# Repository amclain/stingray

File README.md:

# Stingray

Build farm automation and remote management.

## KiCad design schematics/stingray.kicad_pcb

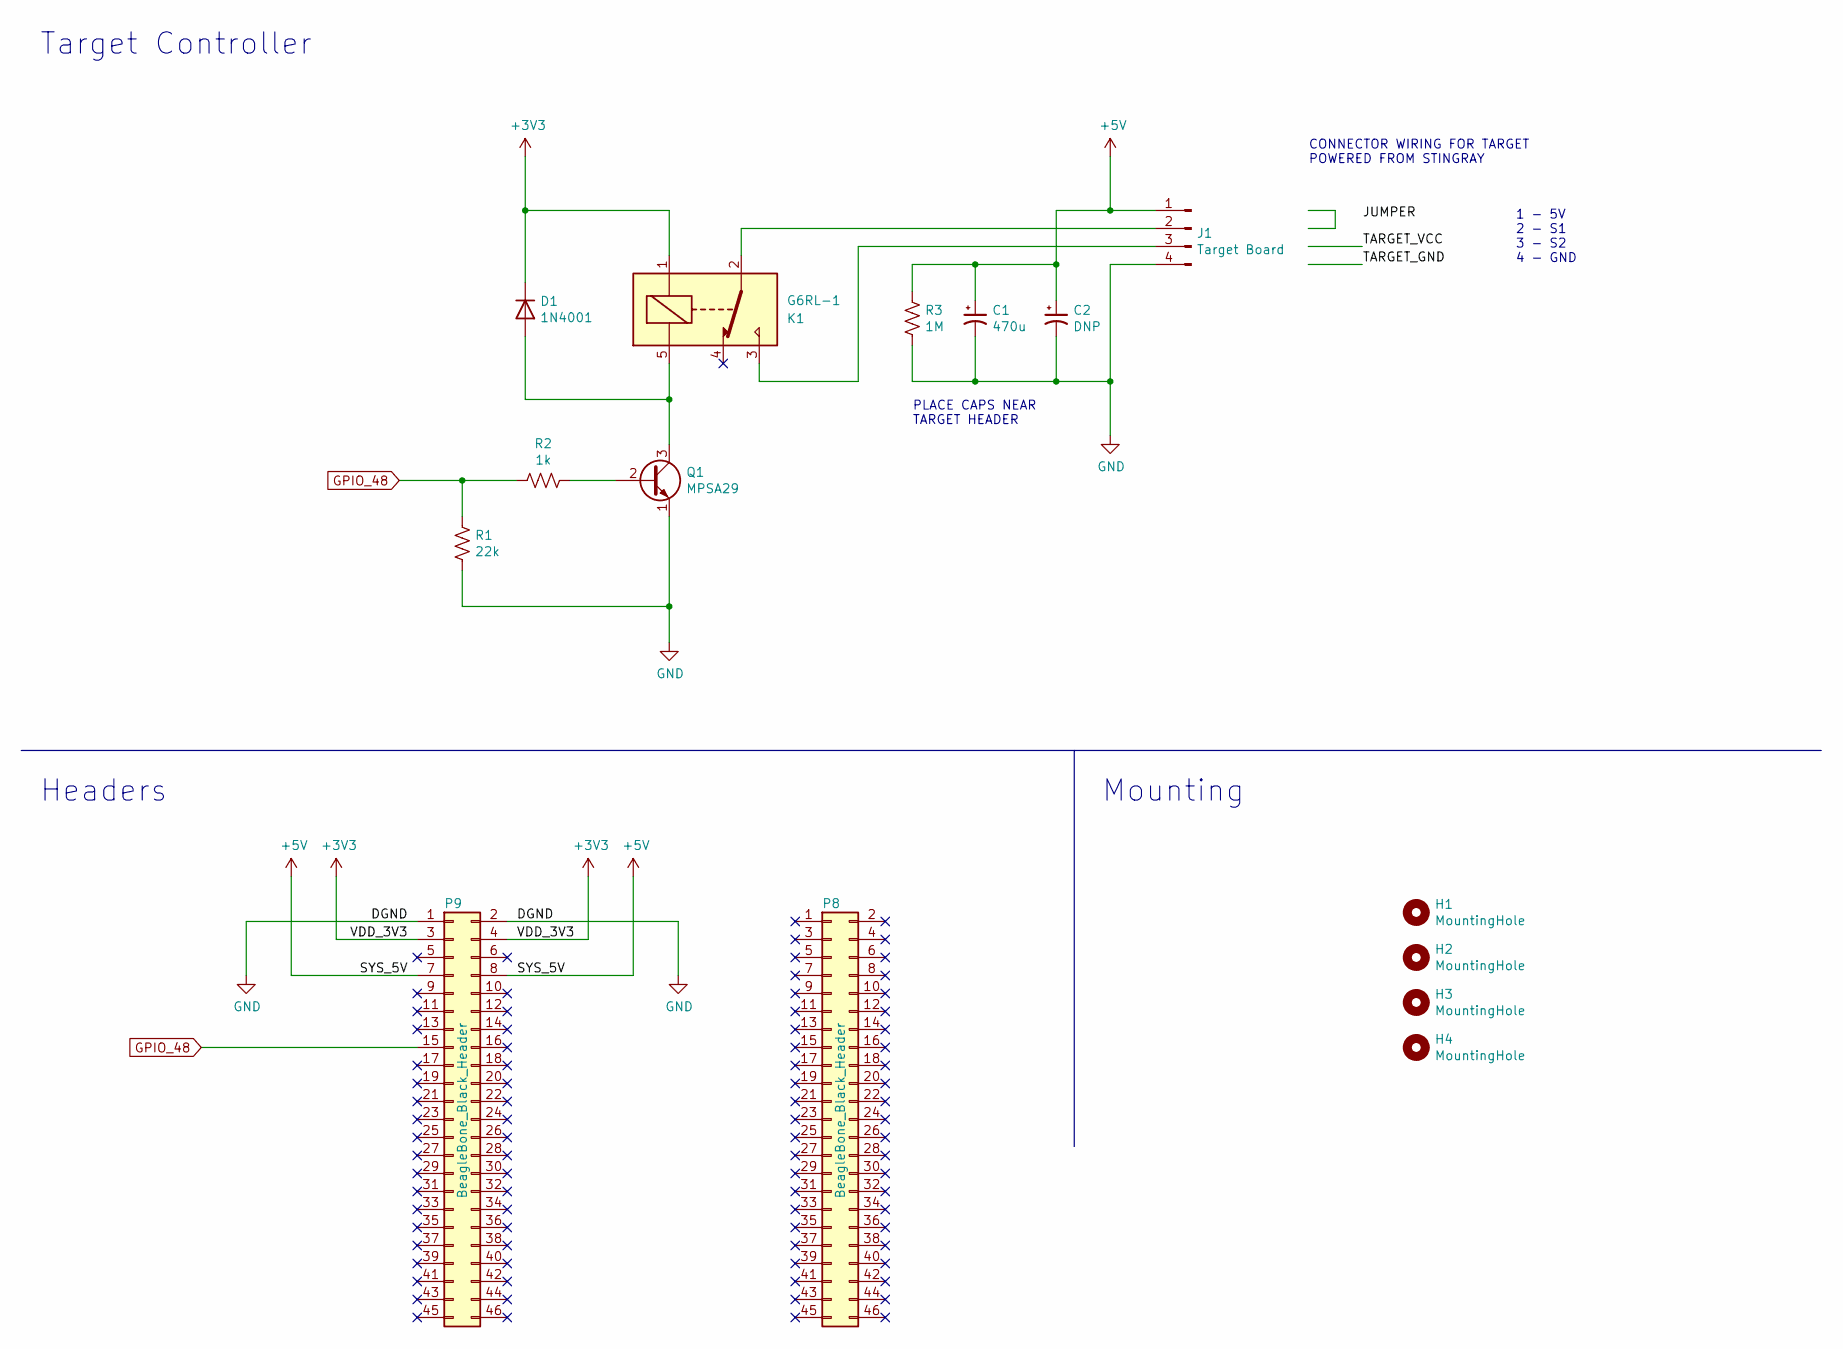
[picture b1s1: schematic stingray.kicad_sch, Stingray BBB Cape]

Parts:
C1: 470u; CP_Radial_D8.0mm_P5.00mm
C2: DNP; CP_Radial_D8.0mm_P5.00mm
D1: 1N4001; D_DO-41_SOD81_P10.16mm_Horizontal
H1, H2, H3, H4: MountingHole; MountingHole_3.2mm_M3
J1: Target Board; PhoenixContact_MC_1,5_4-G-3.81_1x04_P3.81mm_Horizontal
K1: G6RL-1; Relay_SPDT_Omron_G6RL-1
P8, P9: BeagleBone_Black_Header; Socket_BeagleBone_Black
Q1: MPSA29; TO-92_Inline
R1: 22k; R_Axial_DIN0207_L6.3mm_D2.5mm_P10.16mm_Horizontal
R2: 1k; R_Axial_DIN0207_L6.3mm_D2.5mm_P10.16mm_Horizontal
R3: 1M; R_Axial_DIN0207_L6.3mm_D2.5mm_P10.16mm_Horizontal

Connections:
+3V3: D1.1 (K), K1.1, P9.3, P9.4
+5V: C1.1, C2.1, J1.1, P9.7, P9.8, R3.1
GND: C1.2, C2.2, J1.4, P9.1, P9.2, Q1.1 (E), R1.2, R3.2
GPIO_48: P9.15, R1.1, R2.2
unnamed: D1.2 (A), K1.5, Q1.3 (C)
unnamed: J1.2, K1.2
unnamed: J1.3, K1.3
unnamed: Q1.2 (B), R2.1

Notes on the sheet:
Headers
Target Controller
1 - 5V 2 - S1 3 - S2 4 - GND
Mounting
PLACE CAPS NEAR TARGET HEADER
CONNECTOR WIRING FOR TARGET POWERED FROM STINGRAY

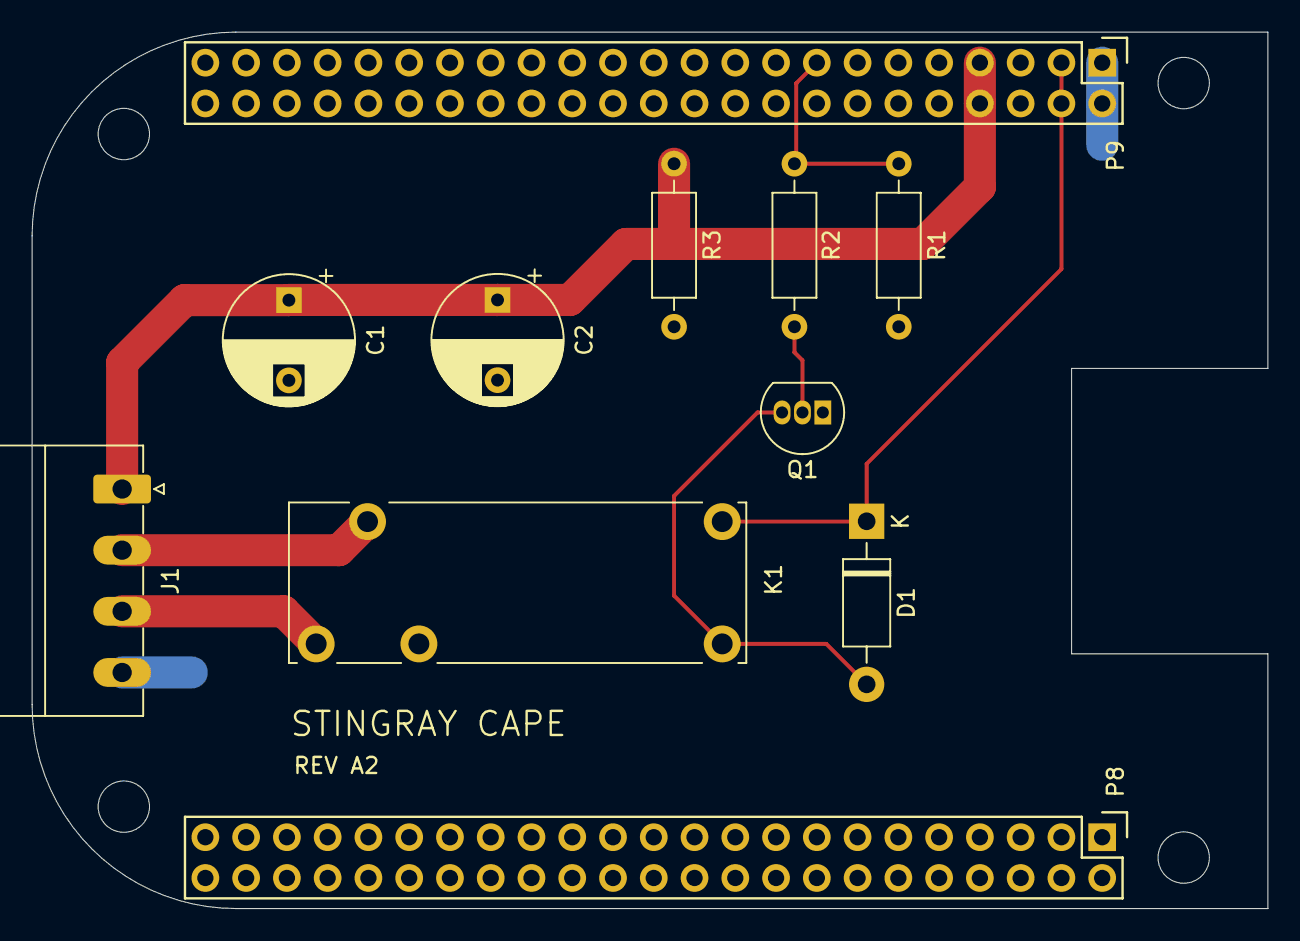
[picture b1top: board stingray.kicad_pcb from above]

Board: 2 copper layers, 77.0 x 54.6 mm, 15 parts (0 on the bottom side), 8 nets.

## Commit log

2022-11-20 Project setup
2022-11-20 Add ExDoc
2022-11-20 Disable formatter
2022-11-20 Set up CI
2022-11-20 Add code coverage
2022-11-20 Add dialyzer
2022-11-20 Add ability to set Nerves system path from env var
2022-11-20 Add ESpec
2022-11-20 Split config files by target and env
2022-11-20 Add a target
2022-11-20 List targets
2022-11-20 Remove a target
2022-11-20 Get a target
2022-11-20 Alias Target in IEx
2022-11-20 Update MOTD
2022-11-20 Update hostname
2022-11-20 Remove irrelevant mDNS services
2022-11-24 Hide coverage warnings when running tests
2022-11-24 Decompose Console into a client API and server
2022-11-24 Can set properties of an existing target
2022-11-24 Prototype of opening a console to a target
2022-11-24 Add stinger to IEx prompt
    This helps differentiate which prompt the user is in when consoling
    into other devices.
2022-11-24 Add serial port baud rate to target
2022-11-24 Refactor Target.add
2022-11-24 Updated console server to take an absolute serial device path
2022-11-25 Update error when console server stops if serial port is not found
2022-11-25 Add console server tests
2022-11-25 Switch DI from agent to ETS table
    ETS table allows concurrent reads.
2022-11-25 Add DI revert function
2022-11-25 Refactor console command parser into its own module
2022-11-25 Send console commands through console server
2022-11-26 Add command to enter U-Boot console
2022-11-26 Enter a U-Boot console that requires a key string
2022-11-27 Disable BBB heartbeat LED
2022-12-04 Add runtime config
2022-12-04 Open port in binary mode
2022-12-04 Get SSH keys from GitHub
2022-12-07 Ignore console byte 254 to prevent BEAM process crash
2022-12-07 Design circuit to control target power
2022-12-11 Turn target power on and off
2022-12-11 DI mappings can be set in the config and compiled
2022-12-11 Split power manager into driver and virtual implementations
2022-12-11 Hide picocom's configuration output
2022-12-11 Add the ability to power cycle a target
2022-12-12 Update nerves_system_br
2022-12-23 Update CI to use the nerves_system_stingray_bbb GitHub repo
2022-12-25 Spike NFS
2022-12-25 Update NFS exports API
2022-12-26 Target operations update NFS exports
2022-12-26 Create Stingray firmware upload mix task
2022-12-26 Manage an upload directory for each target
2022-12-26 NFS stops when application stops
2022-12-27 Detect uploaded firmware and unpack to shared directory
2022-12-27 Generate U-Boot env vars for a target
2022-12-27 Use nerves_system_stingray_bbb v1.0.2
2022-12-28 Move DI to its own library (resolve) and update config
    https://hex.pm/packages/resolve
2022-12-28 Replace relay with a mosfet
2022-12-28 Invert GPIO power signal
2022-12-29 Reformat Target.add
2022-12-30 Revert to relay design and modify for active high
2023-01-08 Design single target PCB
2023-01-08 Generate gerbers for single target PCB
2023-01-10 Schematic cleanup
2023-01-13 Refactor Target.add to use CubDB.get_and_update
2023-02-27 PCB rev A2
